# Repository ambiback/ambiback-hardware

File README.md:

# AmbiBack Hardware

**English** · [Deutsch](README.de.md)

PCB design files for the [AmbiBack project](https://github.com/ambiback). The LED controller PCB v0r1 holds an M5Stack Atom Lite running the [AmbiBack firmware](https://github.com/ambiback/ambiback-firmware).

**PCB design:** [Andreas "Andy" Hofmann](https://github.com/ezcGman), 2021, published with his consent.

| Top | Bottom |
| --- | --- |
|  |  |

The images are rendered from the Gerber files in this repository. They are not photos, and the colors do not show a real board.

## Status

- Prototype revision v0r1. Review the design before ordering boards.
- **The board has not been tested with the current firmware.**
- **LED data pin mismatch:** The board routes LED data to `G33`, but the firmware target `ESP32_M5ST_ATOMLITE` uses GPIO 26 by default. With this board, `LEDCTRL_PIN` in `globalincludes.h` has to be changed to `33`. This change has not been tested.
- AmbiBack devices have not been on sale for around five years. This repository is for DIY use, with no product support. More at [ambiback.de](https://www.ambiback.de/).

## LED controller PCB v0r1

- Board size: 40 × 50 mm
- Socket for an M5Stack Atom Lite
- 5 V power input through a two-pin screw terminal, with a fuse on the board
- Four-pin LED screw terminal labeled `+5V`, `LED`, `LED`, `GND`
- Micro-USB socket that does not power the board. Its 5 V line reaches an Atom pin through a diode and resistor as the signal `USB-CHK`.

## Files

| Path | Content |
| --- | --- |
| [`led-control-v0r1/kicad/`](led-control-v0r1/kicad/) | KiCad 5 project |
| [`led-control-v0r1/gerber/`](led-control-v0r1/gerber/) | Gerber and drill files for manufacturing |
| [`images/`](images/) | Renderings of both sides |

The project uses footprints from [andys-footprints](https://github.com/ezcGman/andys-footprints). Local file paths were removed from the netlist. The design itself is unchanged.

## License

Copyright (C) 2021 Andreas Hofmann

The PCB data and the images derived from it are licensed under [Creative Commons Attribution-NonCommercial-ShareAlike 4.0 International (CC BY-NC-SA 4.0)](https://creativecommons.org/licenses/by-nc-sa/4.0/), see [LICENSE.txt](LICENSE.txt). Commercial use is not permitted. They are provided as is and without warranty.

M5Stack is a trademark of its owner and is named only to describe compatibility. This project is not affiliated with it.

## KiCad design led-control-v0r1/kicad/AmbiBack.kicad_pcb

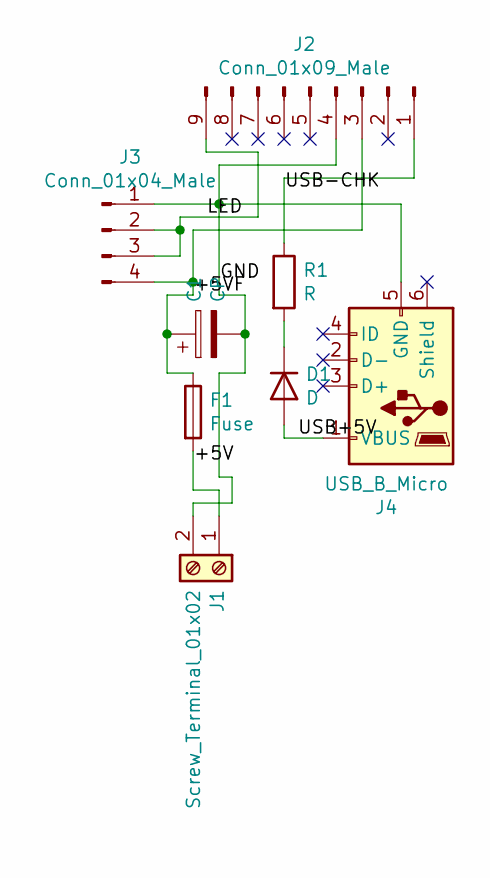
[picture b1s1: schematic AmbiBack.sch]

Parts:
C1: CP; CP_Radial_D10.0mm_P5.00mm
D1: D; D_SMA_Handsoldering
F1: Fuse; Fuse_1808_4520Metric
J1: Screw_Terminal_01x02; TerminalBlock_bornier-2_P5.08mm
J2: Conn_01x09_Male; M5-Stack-Atomic-DIY-Proto-PCB-With-Mounting-Hole
J3: Conn_01x04_Male; TerminalBlock_bornier-4_P5.08mm
J4: USB_B_Micro; USB_Micro-B_Molex-105017-0001
R1: R; R_0805_2012Metric_Pad1.20x1.40mm_HandSolder

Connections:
/+5V: F1.2, J1.1
/+5VF: C1.1, F1.1, J2.3, J3.4
/GND: C1.2, J1.2, J2.4, J3.1, J4.5 (GND)
/LED: J2.9, J3.2, J3.3
/USB+5V: D1.2 (A), J4.1 (VBUS)
/USB-CHK: J2.1, R1.1
unnamed: D1.1 (K), R1.2

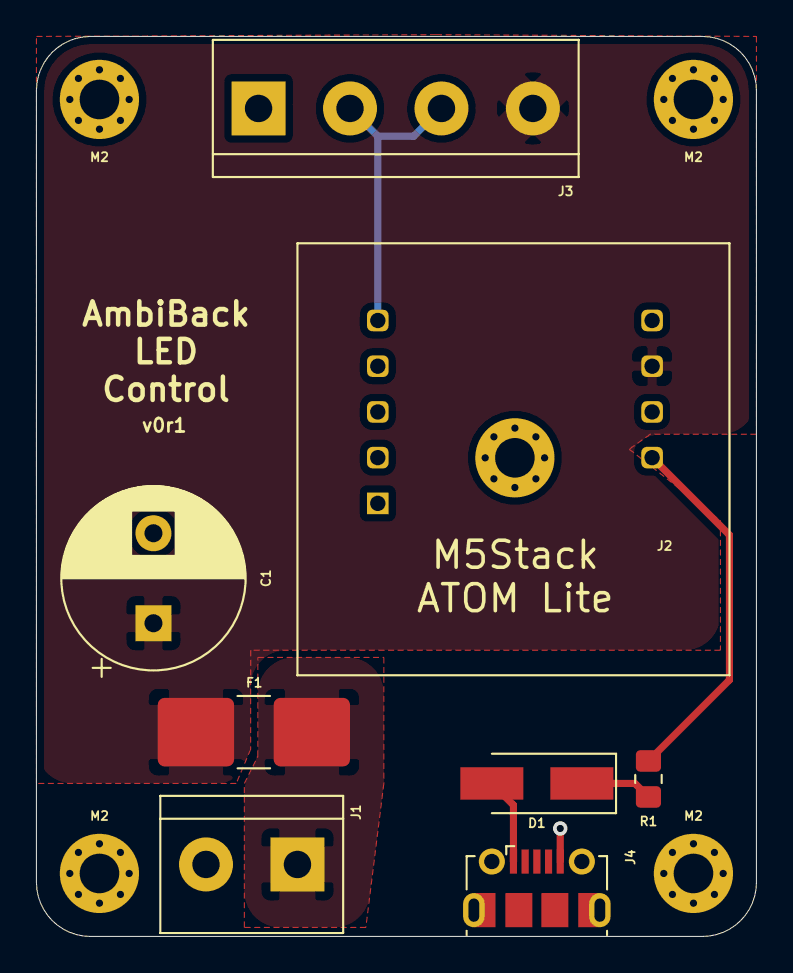
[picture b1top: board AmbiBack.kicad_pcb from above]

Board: 2 copper layers, 40.0 x 50.0 mm, 12 parts (0 on the bottom side), 7 nets.

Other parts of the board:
M2, M2#2, M2#3, M2#4: MountingHole_2.2mm_M2_Pad_Via
